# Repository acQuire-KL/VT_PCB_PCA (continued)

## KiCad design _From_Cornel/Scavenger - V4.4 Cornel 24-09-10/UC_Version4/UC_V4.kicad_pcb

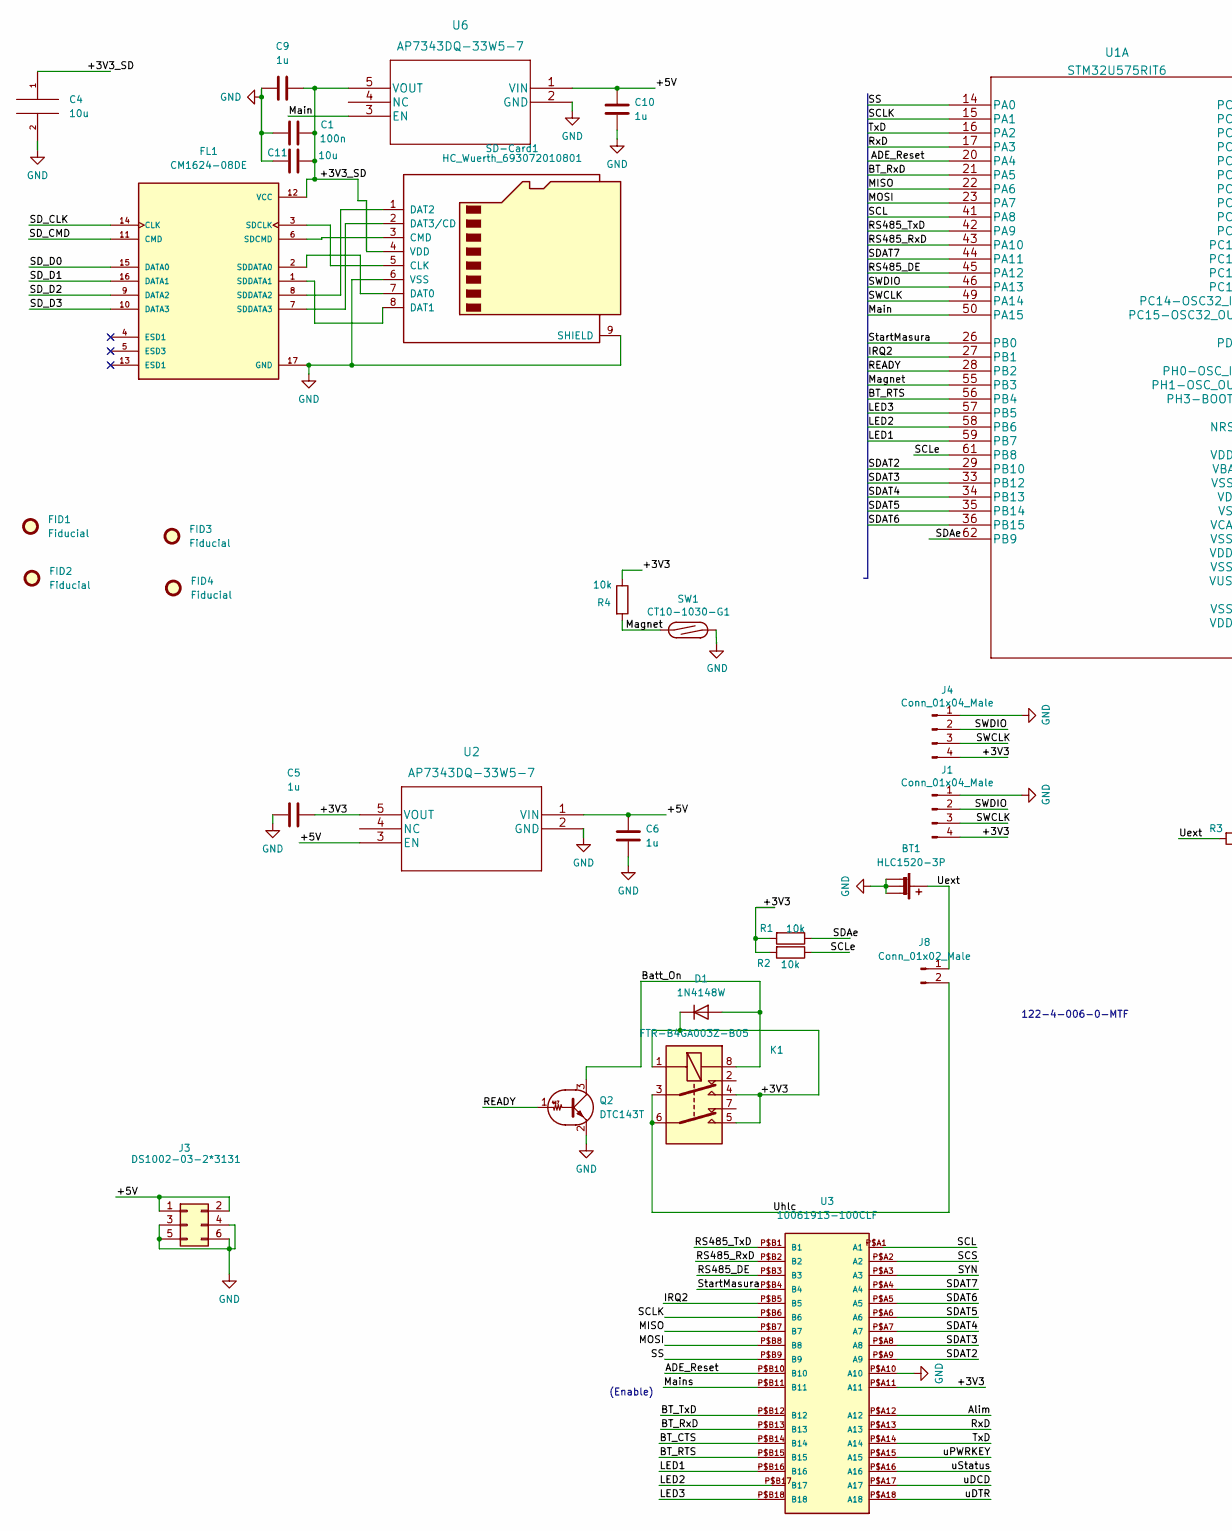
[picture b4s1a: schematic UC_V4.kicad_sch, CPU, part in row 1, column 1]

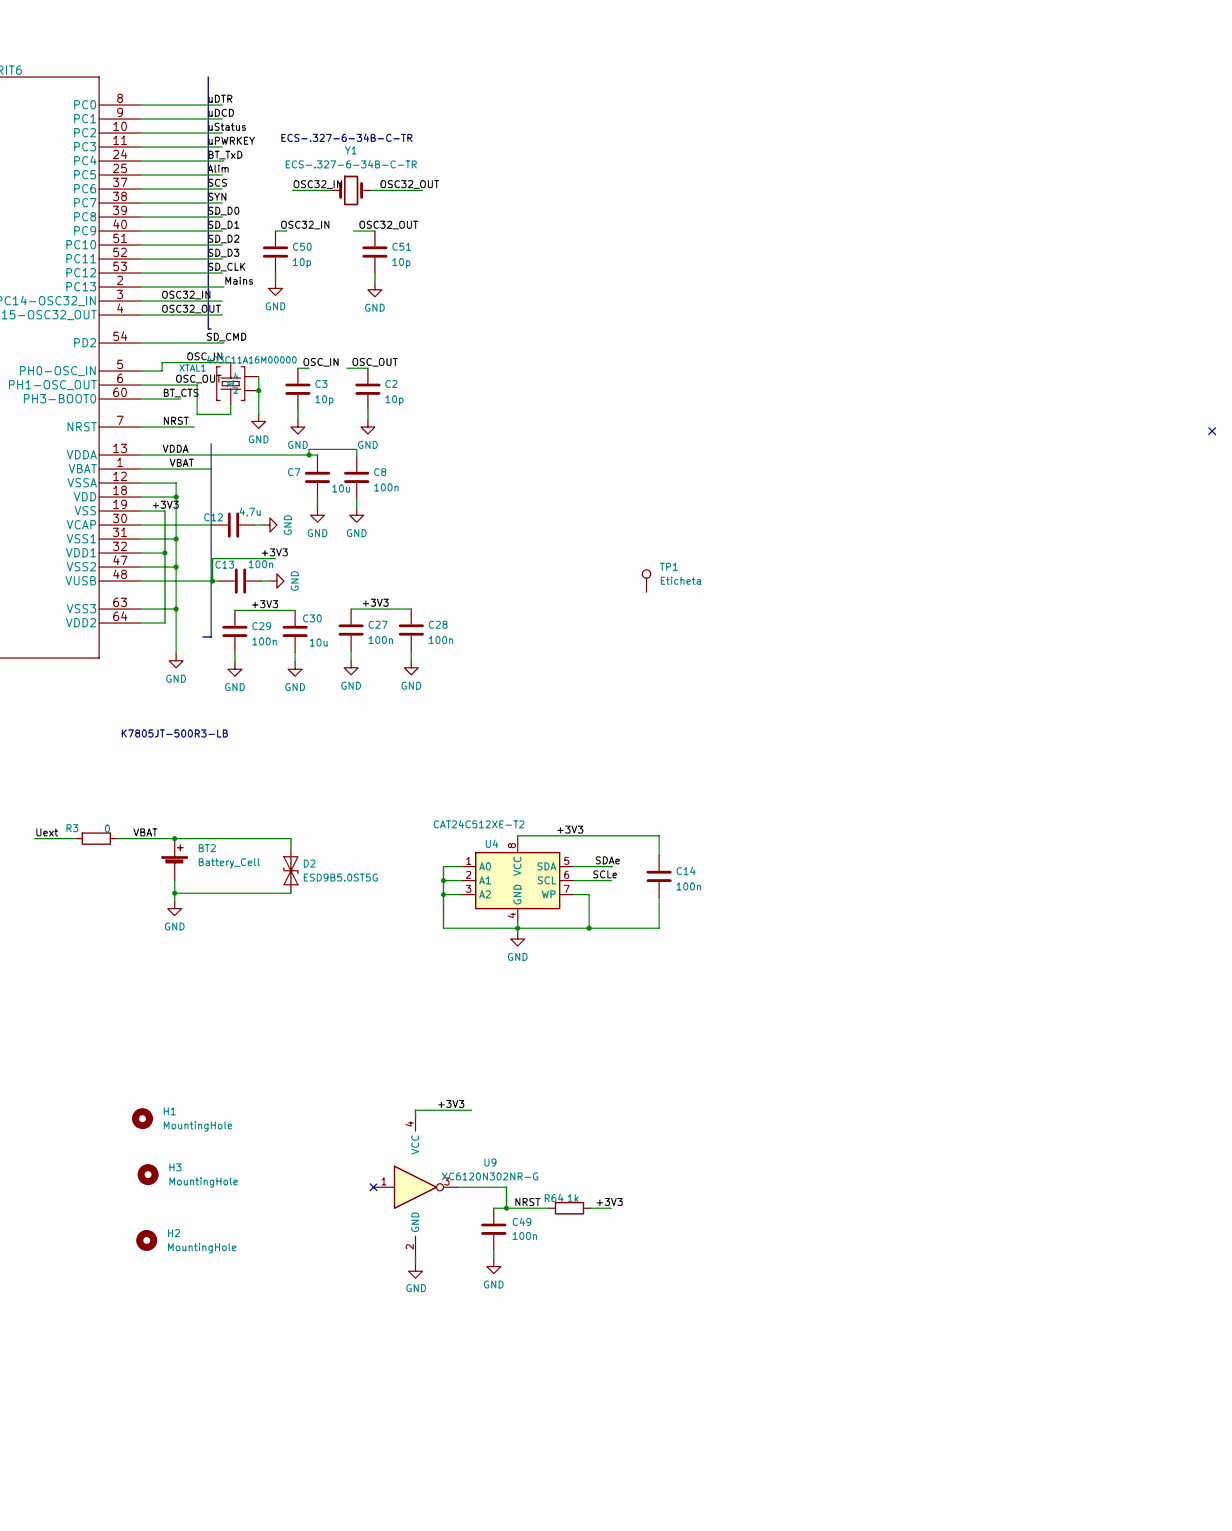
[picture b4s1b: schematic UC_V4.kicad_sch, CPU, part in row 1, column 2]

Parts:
BT1: HLC1520-3P
BT2: Battery_Cell; BatteryHolder_Keystone_3002_1x2032
C1, C8, C13, C14, C27, C28, C29, C49: 100n; C_0603_1608Metric
C2, C3, C50, C51: 10p; C_0603_1608Metric
C4, C7, C11, C30: 10u; C_1206_3216Metric
C5, C6, C9, C10: 1u; C_0603_1608Metric
C12: 4,7u; C_1206_3216Metric
D1: 1N4148W; D_SOD-123
D2: ESD9B5.0ST5G; SOD-923_ONS
FID1, FID2, FID3, FID4: Fiducial; Fiducial_1mm_Mask2mm
FL1: CM1624-08DE; FIL_CM1624; PARTREV 4
H1, H2, H3: MountingHole; MountingHole_3.2mm_Simpla
J1: Conn_01x04_Male; A_PinHeader_1x04_P2.54mm_Test
J3: DS1002-03-2*3131; PinSocket_2x03_P2.54mm_Vertical
J4: Conn_01x04_Male; PinHeader_1x04_P2.54mm_Vertical
J8: Conn_01x02_Male; PinHeader_1x02_P2.54mm_Vertical
K1: FTR-B4GA003Z-B05; Relay_Fujitsu_FTR-B4GA003
Q2: DTC143T; SOT-23
R1, R2, R4: 10k; R_0603_1608Metric
R3: 0; R_0603_1608Metric
R64: 1k; R_0603_1608Metric
SD-Card1: HC_Wuerth_693072010801; microSD_HC_Wuerth_693072010801
SW1: CT10-1030-G1; SW_SPST_REED_CT10-XXXX-G1
TP1: Eticheta
U1: STM32U575RIT6; LQFP-64_10x10mm_P0.5mm
U2, U6: AP7343DQ-33W5-7; AP3012KTR-G1
U3: 10061913-100CLF; MPN 10061913-100CLF
U4: CAT24C512XE-T2; SO-8_3.9x4.9mm_P1.27mm
U9: XC6120N302NR-G; SC-82AA
XTAL1: 403C11A16M00000; Crystal_SMD_SeikoEpson_TSX3225-4Pin_3.2x2.5mm
Y1: ECS-.327-6-34B-C-TR; Crystal_SMD_EuroQuartz_EQ161-2Pin_3.2x1.5mm

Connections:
/+3V3: C5.2, C13.1, C14.1, C27.1, C28.1, C29.1, C30.1, D1.1 (K), J1.4, J4.4, K1.1, K1.4, K1.5, R1.2, R2.2, R4.1, R64.1, U1.19 (VSS), U1.32 (VDD1), U1.48 (VUSB), U1.64 (VDD2), U2.5 (VOUT), U3.P$A11 (A11), U4.8 (VCC), U9.4 (VCC)
/+3V3_SD: C1.2, C4.1, C9.2, C11.2, FL1.12 (VCC), SD-Card1.4 (VDD), U6.5 (VOUT)
/+5V: C6.1, C10.1, J3.1, J3.2, U2.1 (VIN), U2.3 (EN), U6.1 (VIN)
/ADE_Reset: U1.20 (PA4), U3.P$B10 (B10)
/Alim: U1.25 (PC5), U3.P$A12 (A12)
/BT_CTS: U1.60 (PH3-BOOT0), U3.P$B14 (B14)
/BT_RTS: U1.56 (PB4), U3.P$B15 (B15)
/BT_RxD: U1.21 (PA5), U3.P$B13 (B13)
/BT_TxD: U1.24 (PC4), U3.P$B12 (B12)
/Batt_On: D1.2 (A), K1.8, Q2.3 (C)
/IRQ2: U1.27 (PB1), U3.P$B5 (B5)
/LED1: U1.59 (PB7), U3.P$B16 (B16)
/LED2: U1.58 (PB6), U3.P$B17 (B17)
/LED3: U1.57 (PB5), U3.P$B18 (B18)
/MISO: U1.22 (PA6), U3.P$B7 (B7)
/MOSI: U1.23 (PA7), U3.P$B8 (B8)
/Magnet: R4.2, SW1.1, U1.55 (PB3)
/Main: U1.50 (PA15), U6.3 (EN)
/Mains: U1.2 (PC13), U3.P$B11 (B11)
/NRST: C49.1, R64.2, U1.7 (NRST), U9.3
/OSC32_IN: C50.1, U1.3 (PC14-OSC32_IN), Y1.1
/OSC32_OUT: C51.1, U1.4 (PC15-OSC32_OUT), Y1.2
/OSC_IN: C3.1, U1.5 (PH0-OSC_IN), XTAL1.3
/OSC_OUT: C2.1, U1.6 (PH1-OSC_OUT), XTAL1.1
/READY: Q2.1 (B), U1.28 (PB2)
/RS485_DE: U1.45 (PA12), U3.P$B3 (B3)
/RS485_RxD: U1.43 (PA10), U3.P$B2 (B2)
/RS485_TxD: U1.42 (PA9), U3.P$B1 (B1)
/RxD: U1.17 (PA3), U3.P$A13 (A13)
/SCL: U1.41 (PA8), U3.P$A1 (A1)
/SCLK: U1.15 (PA1), U3.P$B6 (B6)
/SCLe: R2.1, U1.61 (PB8), U4.6 (SCL)
/SCS: U1.37 (PC6), U3.P$A2 (A2)
/SDAT2: U1.29 (PB10), U3.P$A9 (A9)
/SDAT3: U1.33 (PB12), U3.P$A8 (A8)
/SDAT4: U1.34 (PB13), U3.P$A7 (A7)
/SDAT5: U1.35 (PB14), U3.P$A6 (A6)
/SDAT6: U1.36 (PB15), U3.P$A5 (A5)
/SDAT7: U1.44 (PA11), U3.P$A4 (A4)
/SDAe: R1.1, U1.62 (PB9), U4.5 (SDA)
/SD_CLK: FL1.14 (CLK), U1.53 (PC12)
/SD_CMD: FL1.11 (CMD), U1.54 (PD2)
/SD_D0: FL1.15 (DATA0), U1.39 (PC8)
/SD_D1: FL1.16 (DATA1), U1.40 (PC9)
/SD_D2: FL1.9 (DATA2), U1.51 (PC10)
/SD_D3: FL1.10 (DATA3), U1.52 (PC11)
/SS: U1.14 (PA0), U3.P$B9 (B9)
/SWCLK: J1.3, J4.3, U1.49 (PA14)
/SWDIO: J1.2, J4.2, U1.46 (PA13)
/SYN: U1.38 (PC7), U3.P$A3 (A3)
/StartMasura: U1.26 (PB0), U3.P$B4 (B4)
/TxD: U1.16 (PA2), U3.P$A14 (A14)
/Uext: BT1.1 (+), J8.1, R3.2
/Uhlc: J8.2, K1.3, K1.6
/VBAT: BT2.1 (+), D2.2 (A2), R3.1, U1.1 (VBAT)
/VDDA: C7.1, C8.1, U1.13 (VDDA)
/uDCD: U1.9 (PC1), U3.P$A17 (A17)
/uDTR: U1.8 (PC0), U3.P$A18 (A18)
/uPWRKEY: U1.11 (PC3), U3.P$A15 (A15)
/uStatus: U1.10 (PC2), U3.P$A16 (A16)
GND: BT1.2 (-), BT1.3 (-), BT1.4 (-), BT2.2 (-), C1.1, C2.2, C3.2, C4.2, C5.1, C6.2, C7.2, C8.2, C9.1, C10.2, C11.1, C12.2, C13.2, C14.2, C27.2, C28.2, C29.2, C30.2, C49.2, C50.2, C51.2, D2.1 (A1), FL1.17 (GND), J1.1, J3.3, J3.4, J3.5, J3.6, J4.1, Q2.2 (E), SD-Card1.6 (VSS), SD-Card1.9 (SHIELD), SW1.2, U1.12 (VSSA), U1.18 (VDD), U1.31 (VSS1), U1.47 (VSS2), U1.63 (VSS3), U2.2 (GND), U3.P$A10 (A10), U4.1 (A0), U4.2 (A1), U4.3 (A2), U4.4 (GND), U4.7 (WP), U6.2 (GND), U9.2 (GND), XTAL1.2, XTAL1.4
unnamed: C12.1, U1.30 (VCAP)
unnamed: FL1.1 (SDDATA1), SD-Card1.8 (DAT1)
unnamed: FL1.2 (SDDATA0), SD-Card1.7 (DAT0)
unnamed: FL1.3 (SDCLK), SD-Card1.5 (CLK)
unnamed: FL1.6 (SDCMD), SD-Card1.3 (CMD)
unnamed: FL1.7 (SDDATA3), SD-Card1.2 (DAT3/CD)
unnamed: FL1.8 (SDDATA2), SD-Card1.1 (DAT2)

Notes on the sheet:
ECS-.327-6-34B-C-TR
K7805JT-500R3-LB
(Enable)
122-4-006-0-MTF

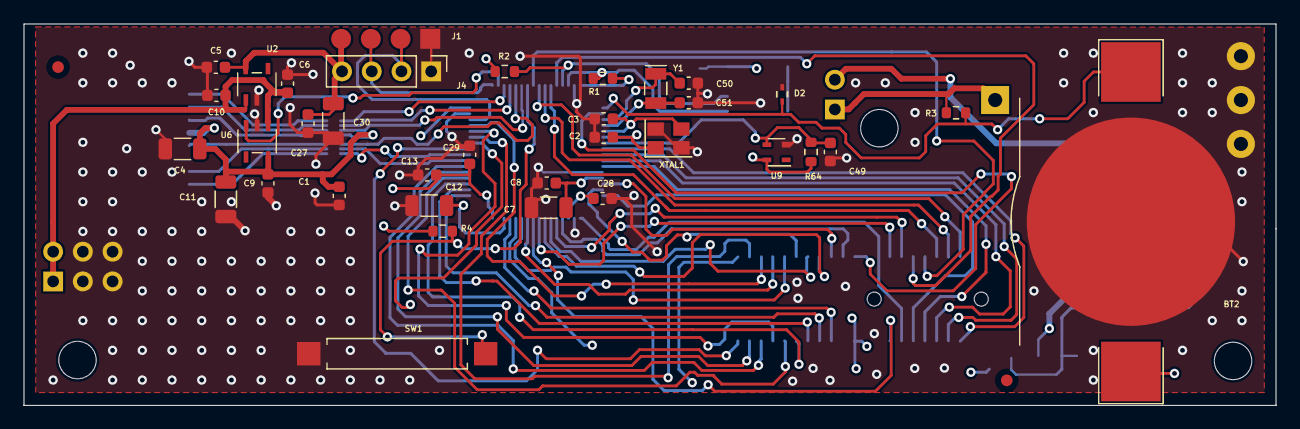
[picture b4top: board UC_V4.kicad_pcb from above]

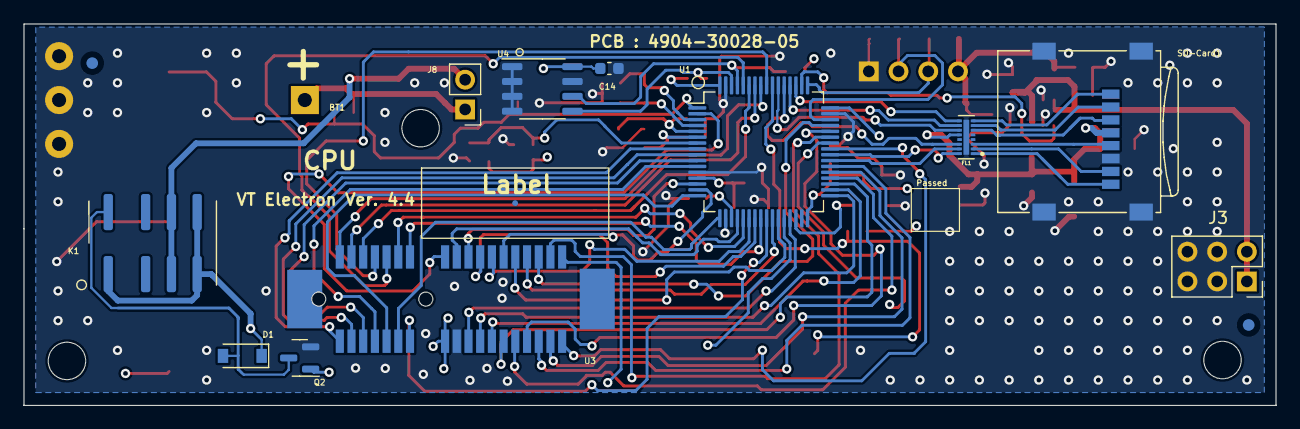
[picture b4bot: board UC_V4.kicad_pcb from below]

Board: 4 copper layers, 107.0 x 32.6 mm, 55 parts (13 on the bottom side), 68 nets.
